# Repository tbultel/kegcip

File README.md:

# kegcip

CIP controller for Beer Tanks and Kegs

Inspired from various existing CIP (Clean In Place) Open Source projects, this one
aim to be a kind of best-off, leveraging the original designers spirit and 
brilliant ideas, but trying to bring more robustness, and reusability.

We only focus here on the microcontroller code and hardware.

The chosen microcontroler is the Teensy 4.0
The application works fine with Teensy 3.1 as well, but it is end of life and sold out.

For simplicity and readabiliy, the code stronly relies on TeensyThreads https://github.com/ftrias/TeensyThreads

# Setup

You need an arduino + teensy toolchain setup, please see on Teensy site how to make it.
The top Makefile lists the needed librairies, that can be installed, for instance,
via the Arduino IDE.

* U8g2: graphical library for SSD1309 LCD chips. Uses hardware SPI.
* Wire: i2C support (for the relays board)
* DallasTemperature: to read the temperature sensor, needs OneWire
* SPI: see above
* RotaryEncoder: support of rotary buttn plugged on GPIOs
* OneWire: see above
* TeensyThreads: for modern and efficient code !
* Bounce2: de-bouncing GPIO in reads
* EEPROM: support of built-in EEPROM in Teensy board, for horameters

# Building

Clone with recurse option, or perform a 
``` 
git submodule update --init
```
Then it's simple:

``` 
make clean && make -j && make flash
```

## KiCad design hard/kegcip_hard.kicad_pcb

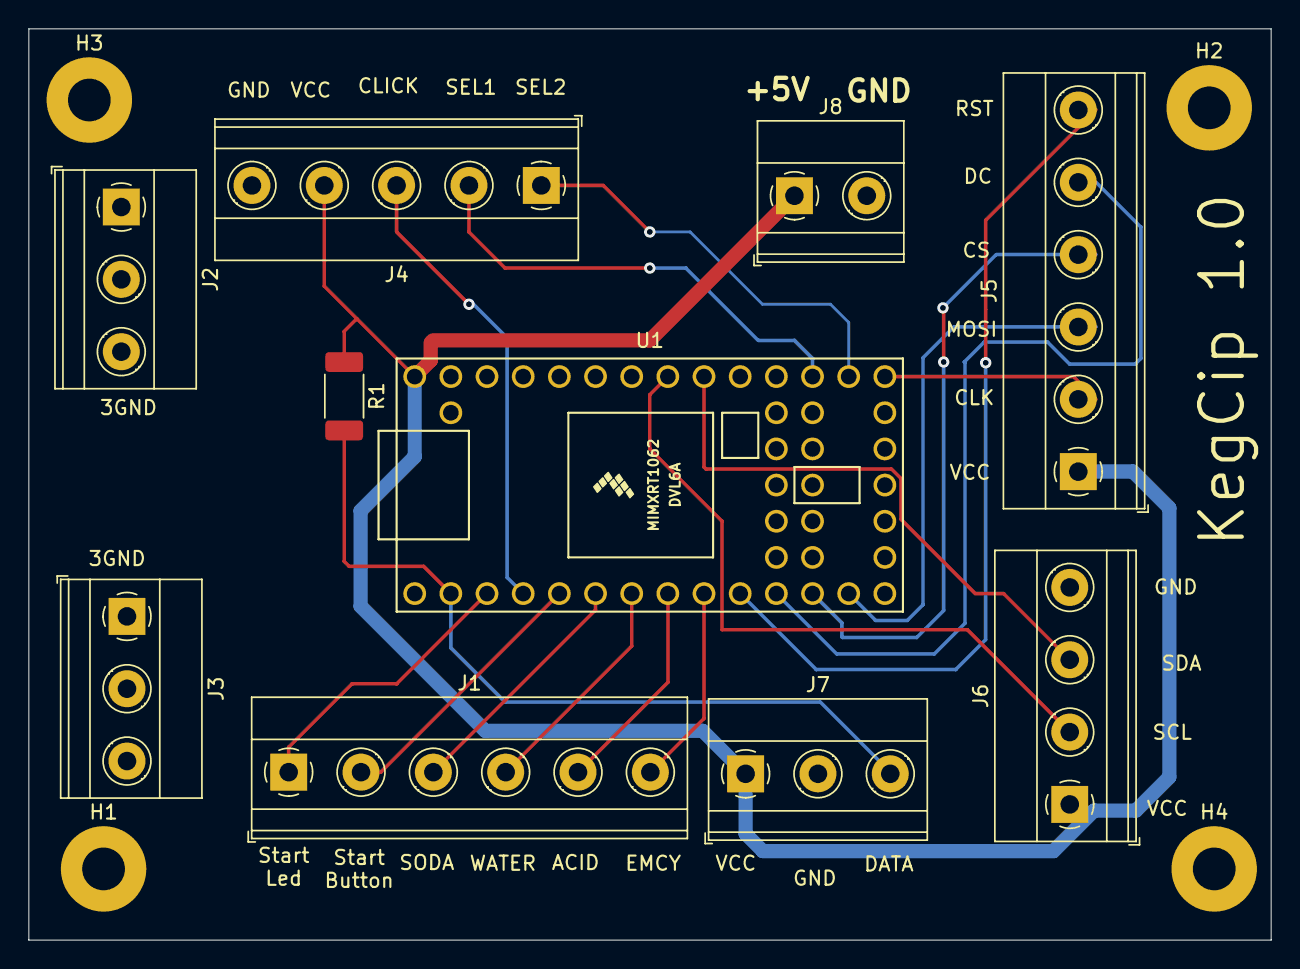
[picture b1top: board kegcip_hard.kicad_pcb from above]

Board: 2 copper layers, 87.2 x 64.0 mm, 14 parts (0 on the bottom side), 19 nets.

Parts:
H1, H2, H3, H4: MountingHole; MountingHole_3mm_Pad
J1: I/O; TerminalBlock_Phoenix_MKDS-1,5-6-5.08_1x06_P5.08mm_Horizont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
J2: GND1; TerminalBlock_Phoenix_MKDS-1,5-3-5.08_1x03_P5.08mm_Horizont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
J3: GND2; TerminalBlock_Phoenix_MKDS-1,5-3-5.08_1x03_P5.08mm_Horizont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
J4: ROTARY; TerminalBlock_Phoenix_MKDS-1,5-5-5.08_1x05_P5.08mm_Horizont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
J5: LCD; TerminalBlock_Phoenix_MKDS-1,5-6-5.08_1x06_P5.08mm_Horizont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
J6: Relays; TerminalBlock_Phoenix_MKDS-1,5-4-5.08_1x04_P5.08mm_Horizont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
J7: Temp; TerminalBlock_Phoenix_MKDS-1,5-3-5.08_1x03_P5.08mm_Horizont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
J8: PWR; TerminalBlock_Phoenix_MKDS-1,5-2-5.08_1x02_P5.08mm_Horizont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
R1: 47k; R_2010_5025Metric_Pad1.40x2.65mm_HandSolder
U1: Teensy4.0; Teensy40

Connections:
+5V: J4.4, J5.1, J6.1, J7.1, J8.1, R1.1, U1.33 (VIN)
/ACID_LOW: J1.5, U1.8 (6_OUT1D)
/EMERGENCY_STOP: J1.6, U1.9 (7_RX2_OUT1A)
/LCD_CLK: J5.2, U1.20 (13_SCK_CRX1_LED)
/LCD_DC: J5.5, U1.11 (9_OUT1C)
/LCD_RST: J5.6, U1.10 (8_TX2_IN1)
/LCD_SPI_CS: J5.4, U1.12 (10_CS_MQSR)
/LCD_SPI_MOSI: J5.3, U1.13 (11_MOSI_CTX1)
/ROT_CLICK: J4.3, U1.4 (2_OUT2)
/ROT_SEL1: J4.2, U1.22 (15_A1_RX3_SPDIF_IN)
/ROT_SEL2: J4.1, U1.21 (14_A0_TX3_SPDIF_OUT)
/SCL: J6.2, U1.26 (19_A5_SCL0)
/SDA: J6.3, U1.25 (18_A4_SDA0)
/SODA_LOW: J1.3, U1.6 (4_BCLK2)
/START_BUTTON: J1.2, U1.5 (3_LRCLK2)
/START_LED: J1.1, U1.3 (1_TX1_CTX2_MISO1)
/TEMP_DATA: J7.3, R1.2, U1.2 (0_RX1_CRX2_CS1)
/WATER_LOW: J1.4, U1.7 (5_IN2)
GND: H1.1, H2.1, H3.1, H4.1, J2.1, J2.2, J2.3, J3.1, J3.2, J3.3, J4.5, J6.4, J7.2, J8.2, U1.1 (GND), U1.17 (GND), U1.32 (GND)

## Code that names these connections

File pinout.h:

#pragma once

// kegcip needs 14 GPIOS and 3 HW spi pins
// (think about when wanting to replace the µC !)

#define PIN_ONE_WIRE_BUS	0

#define PIN_BUTTON_LED		1
#define PIN_MENUCLICK		2
#define PIN_START_BUTTON	3
#define PIN_SODA_LOW		4
#define PIN_WATER_LOW		5
#define PIN_ACID_LOW		6
#define PIN_EMERGENCY_STOP	7

#define PIN_LCD_RST			8
#define PIN_LCD_DC			9
#define PIN_LCD_SPI_CS		10	// HW SPI
#define PIN_LCD_SPI_MOSI	11	// HW SPI
#define PIN_LCD_SPI_CLK		13	// HW SPI

#define PIN_MENUSELECT_1	14
#define PIN_MENUSELECT_2	15

#define PIN_RELAYS_SDA		18
#define PIN_RELAYS_SCL		19

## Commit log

2022-04-04 Added Arduino-Makefile submodule
2022-04-04 Initial version: various I/O and screen tested
2022-04-04 files layout refactoring, 2 functional CIP cycles
2022-04-06 added horameters & diag displays
2022-04-06 fixed horameter display name
2022-04-07 Create LICENSE
2022-04-07 Fix init and menu context swap
2022-04-07 typo
2022-04-07 added support for enzymes temperature
2022-04-08 added support for emergency button
2022-06-20 new cycles, and switched to teensy40
2022-06-20 Update README.md
    Built and set up how-to
2022-06-24 thermo_servo: typo
2022-06-24 relays: moved hardcoded SDA/SCL pin numbers to pinout.h
2022-06-29 Added ack logic, plus sets last input as pullup to get rid of 3.3v
2022-06-29 Added Kicad shematics & pcb
2022-06-29 kegcip.cpp: horameters must be initialized after relays
2022-08-19 thermo servo runway enhancement, simplified cycles, MPC23017 board, fast 1-wire temp request
2022-08-20 rotary button: debounce click
2022-08-26 set internal pullups on i2c lines (effective on teensy4 only)
2022-09-02 removed pullups on SDA and SCL lines
2022-09-02 added thermo test
2022-09-02 thermo_servo: increase heating time limit to 240s, and test time to 1200s
2022-09-09 .gitignore: added vscode & kicad generated files
2022-09-09 Ajout de la circulation pour thermo_test, plus 3 cycles de circulation sans chauffe
2022-09-15 handle emergencies synchronously
2022-09-15 horameter.cpp: fixed compilation error with latest teensy EEPROM library
2022-09-15 Makefile: Changed arduino SDK dir to /opt, and adder USER_LIB_PATH definition
2022-09-15 Added support of docker container
2022-09-16 Achieved build & flash from docker
2022-09-16 Une bonne journée de boulot -> cycle complet futs validé
2022-10-12 thermo servo: put back the temperature to 80 deg
2022-10-12 cycles.cpp: cycle_acide is 10 minutes
2022-10-12 Suppressed whirlpool cycle and water tank
2023-01-03 purge air -> evacuation vers egout
2023-01-10 maintien thermo
2023-01-10 cycles: added simple soda, acid and water purges cycles
2023-01-10 emergency: for thermo_off
2023-01-10 thermo_servo: force thermo_off when runway is detected, and checks the delta only when temp is increasing (will be removed when bubbles are setup
2023-01-11 cycles: Changement tempos amorcage, suppression "Fin eau"
2023-01-11 Meme vidange eau sur rincage et reprise incident
2023-01-17 maintient temp, préchauffage, suppression purge circuit, durées vidange
    => maintient de la température de la soude une fois revenue dans le
    cycle complet fût
    => mais au second cycle si 79,9° alors re-préchauffage avec descente
    de temp (7 minutes pour descendre et remonter !)
    => donc dissociaiton préchauffage de cycle complet
    => problème réccurent d'amorçage sur le cycle complet fûts : la purge
2023-02-17 relays: change to sync always
2023-02-17 thermo: no longer needs the water pump
2023-03-10 Rincage fermenteur : Tempo 5 min au lieu de bouton start
